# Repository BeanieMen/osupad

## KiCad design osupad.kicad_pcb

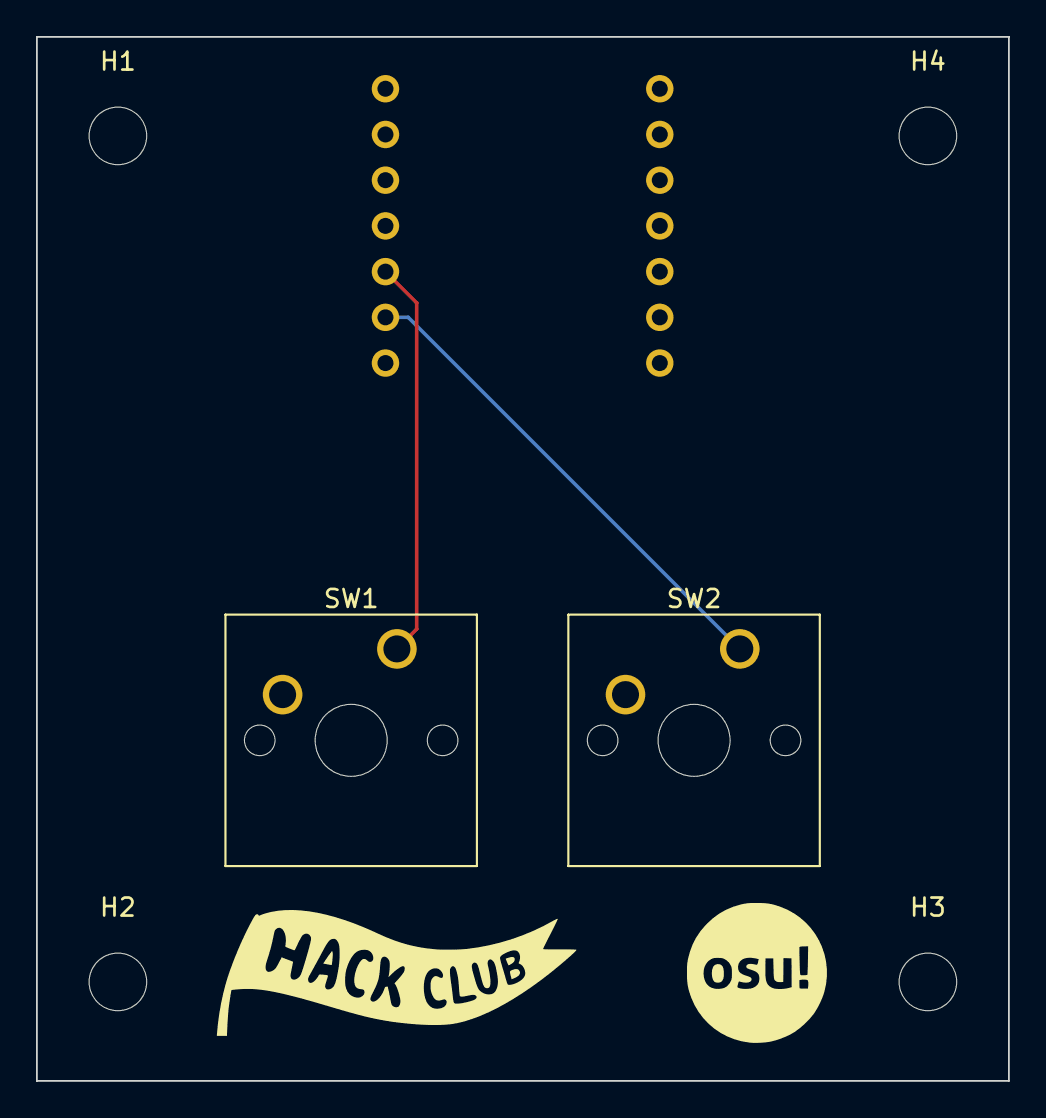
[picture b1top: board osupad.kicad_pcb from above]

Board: 2 copper layers, 54.0 x 58.0 mm, 7 parts (1 on the bottom side), 3 nets.

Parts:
H1, H2, H3, H4: MountingHole_3.2mm_M3
SW1, SW2: SW_Push; SW_Cherry_MX_1.00u_PCB
U1: 102010428; XIAO-RP2040-DIP

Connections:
GND: SW1.2, SW2.2, U1.13 (GND)
unnamed: SW2.1, U1.9 (D8/SCK/P2)
unnamed: SW1.1, U1.10 (D9/MISO/P4)
